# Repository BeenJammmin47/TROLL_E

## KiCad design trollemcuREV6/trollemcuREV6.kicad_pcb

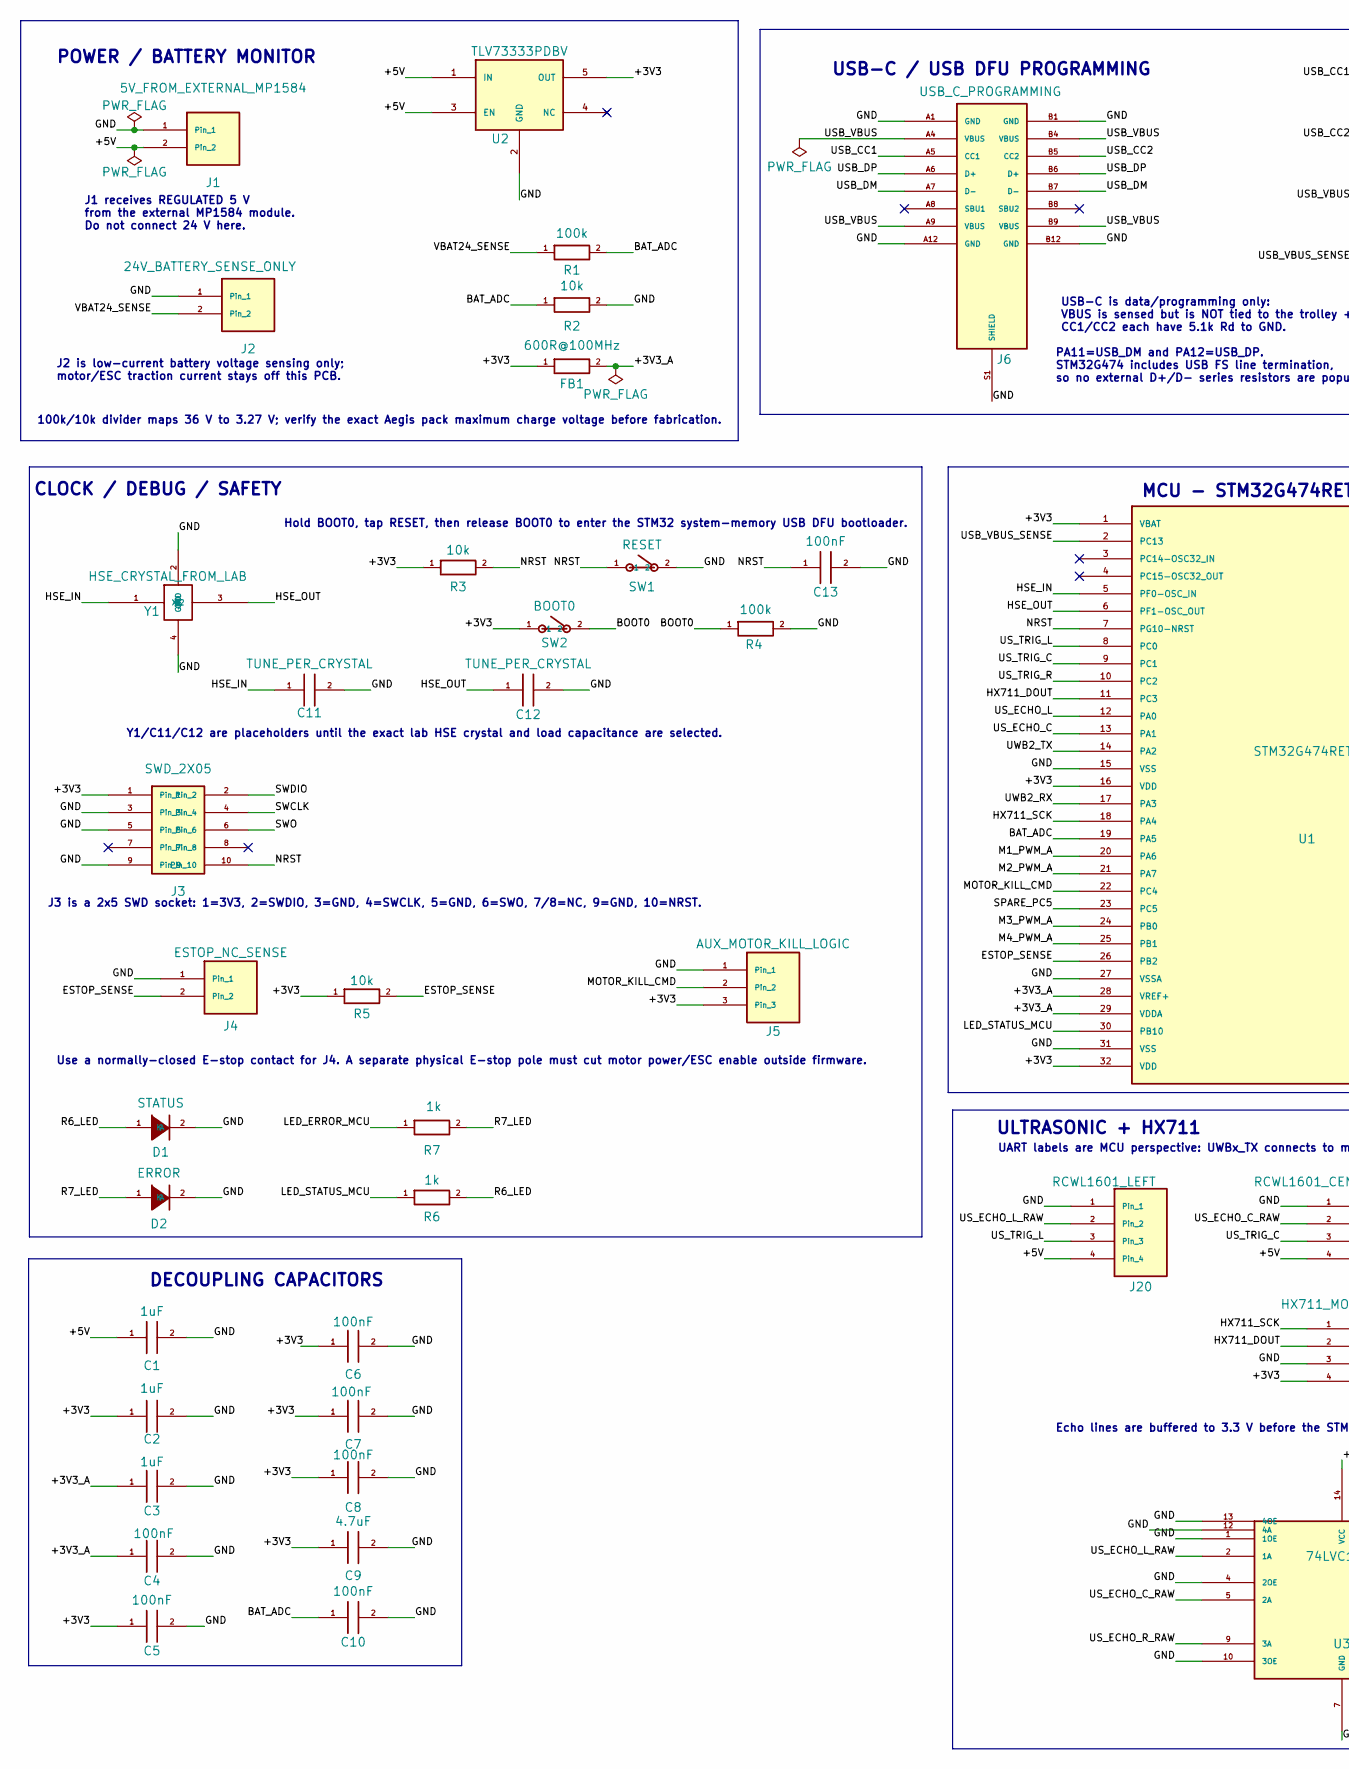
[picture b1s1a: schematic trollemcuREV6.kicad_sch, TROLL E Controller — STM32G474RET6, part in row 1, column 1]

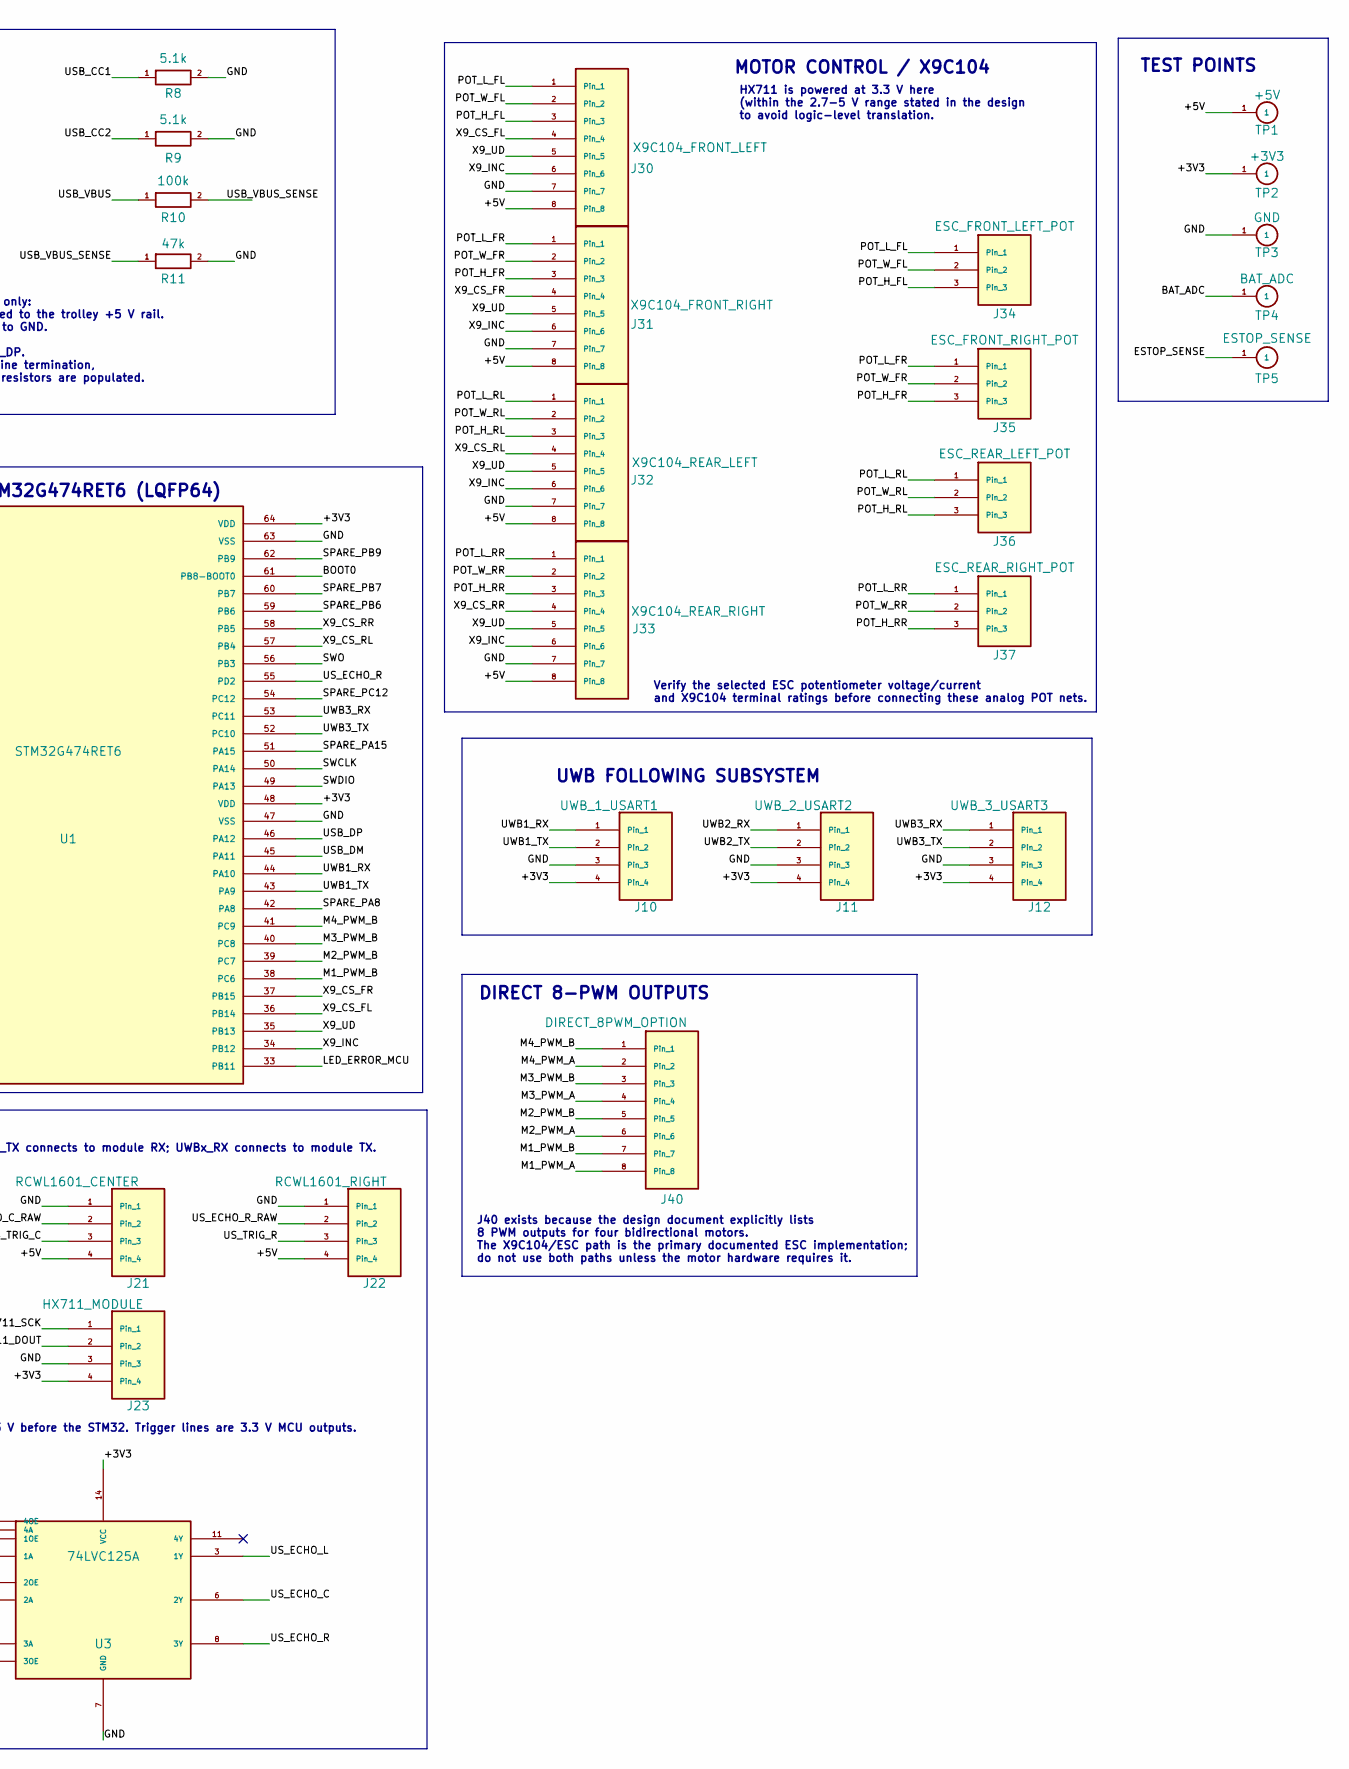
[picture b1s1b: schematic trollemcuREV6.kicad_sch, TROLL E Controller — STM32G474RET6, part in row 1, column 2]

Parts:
C1, C2, C3: 1uF; C_0805_2012Metric
C4, C5, C6, C7, C8, C10, C13: 100nF; C_0805_2012Metric
C9: 4.7uF; C_0805_2012Metric
C11, C12: TUNE_PER_CRYSTAL; C_0805_2012Metric
D1: STATUS; LED_0805_2012Metric
D2: ERROR; LED_0805_2012Metric
FB1: 600R@100MHz; R_0805_2012Metric
J1: 5V_FROM_EXTERNAL_MP1584; PinSocket_1x02_P2.54mm_Vertical
J2: 24V_BATTERY_SENSE_ONLY; PinSocket_1x02_P2.54mm_Vertical
J3: SWD_2X05; PinSocket_2x05_P2.54mm_Vertical
J4: ESTOP_NC_SENSE; PinSocket_1x02_P2.54mm_Vertical
J5: AUX_MOTOR_KILL_LOGIC; PinSocket_1x03_P2.54mm_Vertical
J6: USB_C_PROGRAMMING; USB_C_Receptacle_GCT_USB4085
J10: UWB_1_USART1; PinSocket_1x04_P2.54mm_Vertical
J11: UWB_2_USART2; PinSocket_1x04_P2.54mm_Vertical
J12: UWB_3_USART3; PinSocket_1x04_P2.54mm_Vertical
J20: RCWL1601_LEFT; PinSocket_1x04_P2.54mm_Vertical
J21: RCWL1601_CENTER; PinSocket_1x04_P2.54mm_Vertical
J22: RCWL1601_RIGHT; PinSocket_1x04_P2.54mm_Vertical
J23: HX711_MODULE; PinSocket_1x04_P2.54mm_Vertical
J30: X9C104_FRONT_LEFT; PinHeader_1x08_P2.54mm_Vertical
J31: X9C104_FRONT_RIGHT; PinHeader_1x08_P2.54mm_Vertical
J32: X9C104_REAR_LEFT; PinHeader_1x08_P2.54mm_Vertical
J33: X9C104_REAR_RIGHT; PinHeader_1x08_P2.54mm_Vertical
J34: ESC_FRONT_LEFT_POT; PinSocket_1x03_P2.54mm_Vertical
J35: ESC_FRONT_RIGHT_POT; PinSocket_1x03_P2.54mm_Vertical
J36: ESC_REAR_LEFT_POT; PinSocket_1x03_P2.54mm_Vertical
J37: ESC_REAR_RIGHT_POT; PinSocket_1x03_P2.54mm_Vertical
J40: DIRECT_8PWM_OPTION; PinHeader_1x08_P2.54mm_Vertical
R1, R4, R10: 100k; R_0805_2012Metric
R2, R3, R5: 10k; R_0805_2012Metric
R6, R7: 1k; R_0805_2012Metric
R8, R9: 5.1k; R_0805_2012Metric
R11: 47k; R_0805_2012Metric
SW1: RESET; SW_Push_SPST_NO_Alps_SKRK
SW2: BOOT0; SW_Push_SPST_NO_Alps_SKRK
TP1: +5V; TestPoint_Pad_4.0x4.0mm
TP2: +3V3; TestPoint_Pad_4.0x4.0mm
TP3: GND; TestPoint_Pad_4.0x4.0mm
TP4: BAT_ADC; TestPoint_Pad_4.0x4.0mm
TP5: ESTOP_SENSE; TestPoint_Pad_4.0x4.0mm
U1: STM32G474RET6; LQFP-64_10x10mm_P0.5mm
U2: TLV73333PDBV; SOT-23-5
U3: 74LVC125A; SOIC-14_3.9x8.7mm_P1.27mm
Y1: HSE_CRYSTAL_FROM_LAB; Crystal_SMD_5032-4Pin_5.0x3.2mm

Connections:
/+3V3: C2.1, C5.1, C6.1, C7.1, C8.1, C9.1, FB1.1, J3.1, J5.3, J10.4, J11.4, J12.4, J23.4, R3.1, R5.1, SW2.1, TP2.1 (1_1), U1.1 (VBAT), U1.16 (VDD), U1.32 (VDD), U1.48 (VDD), U1.64 (VDD), U2.5 (OUT), U3.14 (VCC)
/+3V3_A: C3.1, C4.1, FB1.2, U1.28 (VREF+), U1.29 (VDDA)
/+5V: C1.1, J1.2, J20.4, J21.4, J22.4, J30.8, J31.8, J32.8, J33.8, TP1.1 (1_1), U2.1 (IN), U2.3 (EN)
/BAT_ADC: C10.1, R1.2, R2.1, TP4.1 (1_1), U1.19 (PA5)
/BOOT0: R4.1, SW2.2, U1.61 (PB8-BOOT0)
/ESTOP_SENSE: J4.2, R5.2, TP5.1 (1_1), U1.26 (PB2)
/GND: C1.2, C2.2, C3.2, C4.2, C5.2, C6.2, C7.2, C8.2, C9.2, C10.2, C11.2, C12.2, C13.2, D1.2 (K), D2.2 (K), J1.1, J2.1, J3.3, J3.5, J3.9, J4.1, J5.1, J6.A1 (GND_A1), J6.A12 (GND_A12), J6.B1 (GND_B1), J6.B12 (GND_B12), J6.S1 (SHIELD), J6.SH (SHIELD_S1), J10.3, J11.3, J12.3, J20.1, J21.1, J22.1, J23.3, J30.7, J31.7, J32.7, J33.7, R2.2, R4.2, R8.2, R9.2, R11.2, SW1.2, TP3.1 (1_1), U1.15 (VSS), U1.27 (VSSA), U1.31 (VSS), U1.47 (VSS), U1.63 (VSS), U2.2 (GND), U3.1 (1OE), U3.4 (2OE), U3.7 (GND), U3.10 (3OE), U3.12 (4A), U3.13 (4OE), Y1.2 (GND), Y1.4 (GND)
/HSE_IN: C11.1, U1.5 (PF0-OSC_IN), Y1.1 (X1)
/HSE_OUT: C12.1, U1.6 (PF1-OSC_OUT), Y1.3 (X2)
/HX711_DOUT: J23.2, U1.11 (PC3)
/HX711_SCK: J23.1, U1.18 (PA4)
/LED_ERROR_MCU: R7.1, U1.33 (PB11)
/LED_STATUS_MCU: R6.1, U1.30 (PB10)
/M1_PWM_A: J40.8, U1.20 (PA6)
/M1_PWM_B: J40.7, U1.38 (PC6)
/M2_PWM_A: J40.6, U1.21 (PA7)
/M2_PWM_B: J40.5, U1.39 (PC7)
/M3_PWM_A: J40.4, U1.24 (PB0)
/M3_PWM_B: J40.3, U1.40 (PC8)
/M4_PWM_A: J40.2, U1.25 (PB1)
/M4_PWM_B: J40.1, U1.41 (PC9)
/MOTOR_KILL_CMD: J5.2, U1.22 (PC4)
/NRST: C13.1, J3.10, R3.2, SW1.1, U1.7 (PG10-NRST)
/POT_H_FL: J30.3, J34.3
/POT_H_FR: J31.3, J35.3
/POT_H_RL: J32.3, J36.3
/POT_H_RR: J33.3, J37.3
/POT_L_FL: J30.1, J34.1
/POT_L_FR: J31.1, J35.1
/POT_L_RL: J32.1, J36.1
/POT_L_RR: J33.1, J37.1
/POT_W_FL: J30.2, J34.2
/POT_W_FR: J31.2, J35.2
/POT_W_RL: J32.2, J36.2
/POT_W_RR: J33.2, J37.2
/R6_LED: D1.1 (A), R6.2
/R7_LED: D2.1 (A), R7.2
/SPARE_PA8: U1.42 (PA8)
/SPARE_PA15: U1.51 (PA15)
/SPARE_PB6: U1.59 (PB6)
/SPARE_PB7: U1.60 (PB7)
/SPARE_PB9: U1.62 (PB9)
/SPARE_PC5: U1.23 (PC5)
/SPARE_PC12: U1.54 (PC12)
/SWCLK: J3.4, U1.50 (PA14)
/SWDIO: J3.2, U1.49 (PA13)
/SWO: J3.6, U1.56 (PB3)
/USB_CC1: J6.A5 (CC1_A5), R8.1
/USB_CC2: J6.B5 (CC2_B5), R9.1
/USB_DM: J6.A7 (D-_A7), J6.B7 (D-_B7), U1.45 (PA11)
/USB_DP: J6.A6 (D+_A6), J6.B6 (D+_B6), U1.46 (PA12)
/USB_VBUS: J6.A4 (VBUS_A4), J6.A9 (VBUS_A9), J6.B4 (VBUS_B4), J6.B9 (VBUS_B9), R10.1
/USB_VBUS_SENSE: R10.2, R11.1, U1.2 (PC13)
/US_ECHO_C: U1.13 (PA1), U3.6 (2Y)
/US_ECHO_C_RAW: J21.2, U3.5 (2A)
/US_ECHO_L: U1.12 (PA0), U3.3 (1Y)
/US_ECHO_L_RAW: J20.2, U3.2 (1A)
/US_ECHO_R: U1.55 (PD2), U3.8 (3Y)
/US_ECHO_R_RAW: J22.2, U3.9 (3A)
/US_TRIG_C: J21.3, U1.9 (PC1)
/US_TRIG_L: J20.3, U1.8 (PC0)
/US_TRIG_R: J22.3, U1.10 (PC2)
/UWB1_RX: J10.1, U1.44 (PA10)
/UWB1_TX: J10.2, U1.43 (PA9)
/UWB2_RX: J11.1, U1.17 (PA3)
/UWB2_TX: J11.2, U1.14 (PA2)
/UWB3_RX: J12.1, U1.53 (PC11)
/UWB3_TX: J12.2, U1.52 (PC10)
/VBAT24_SENSE: J2.2, R1.1
/X9_CS_FL: J30.4, U1.36 (PB14)
/X9_CS_FR: J31.4, U1.37 (PB15)
/X9_CS_RL: J32.4, U1.57 (PB4)
/X9_CS_RR: J33.4, U1.58 (PB5)
/X9_INC: J30.6, J31.6, J32.6, J33.6, U1.34 (PB12)
/X9_UD: J30.5, J31.5, J32.5, J33.5, U1.35 (PB13)

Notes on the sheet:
TEST POINTS
Verify the selected ESC potentiometer voltage/current and X9C104 terminal ratings before connecting these analog POT nets.
UWB FOLLOWING SUBSYSTEM
USB-C is data/programming only: VBUS is sensed but is NOT tied to the trolley +5 V rail. CC1/CC2 each have 5.1k Rd to GND.
CLOCK / DEBUG / SAFETY
Hold BOOT0, tap RESET, then release BOOT0 to enter the STM32 system-memory USB DFU bootloader.
J2 is low-current battery voltage sensing only; motor/ESC traction current stays off this PCB.
Use a normally-closed E-stop contact for J4. A separate physical E-stop pole must cut motor power/ESC enable outside firmware.
J3 is a 2x5 SWD socket: 1=3V3, 2=SWDIO, 3=GND, 4=SWCLK, 5=GND, 6=SWO, 7/8=NC, 9=GND, 10=NRST.
UART labels are MCU perspective: UWBx_TX connects to module RX; UWBx_RX connects to module TX.
ULTRASONIC + HX711
DIRECT 8-PWM OUTPUTS
DECOUPLING CAPACITORS
J40 exists because the design document explicitly lists 8 PWM outputs for four bidirectional motors. The X9C104/ESC path is the primary documented ESC implementation; do not use both paths unless the motor hardware requires it.
Y1/C11/C12 are placeholders until the exact lab HSE crystal and load capacitance are selected.
MCU - STM32G474RET6 (LQFP64)
USB-C / USB DFU PROGRAMMING
100k/10k divider maps 36 V to 3.27 V; verify the exact Aegis pack maximum charge voltage before fabrication.
J1 receives REGULATED 5 V from the external MP1584 module. Do not connect 24 V here.
PA11=USB_DM and PA12=USB_DP. STM32G474 includes USB FS line termination, so no external D+/D- series resistors are populated.
Echo lines are buffered to 3.3 V before the STM32. Trigger lines are 3.3 V MCU outputs.
POWER / BATTERY MONITOR
MOTOR CONTROL / X9C104
HX711 is powered at 3.3 V here (within the 2.7-5 V range stated in the design to avoid logic-level translation.

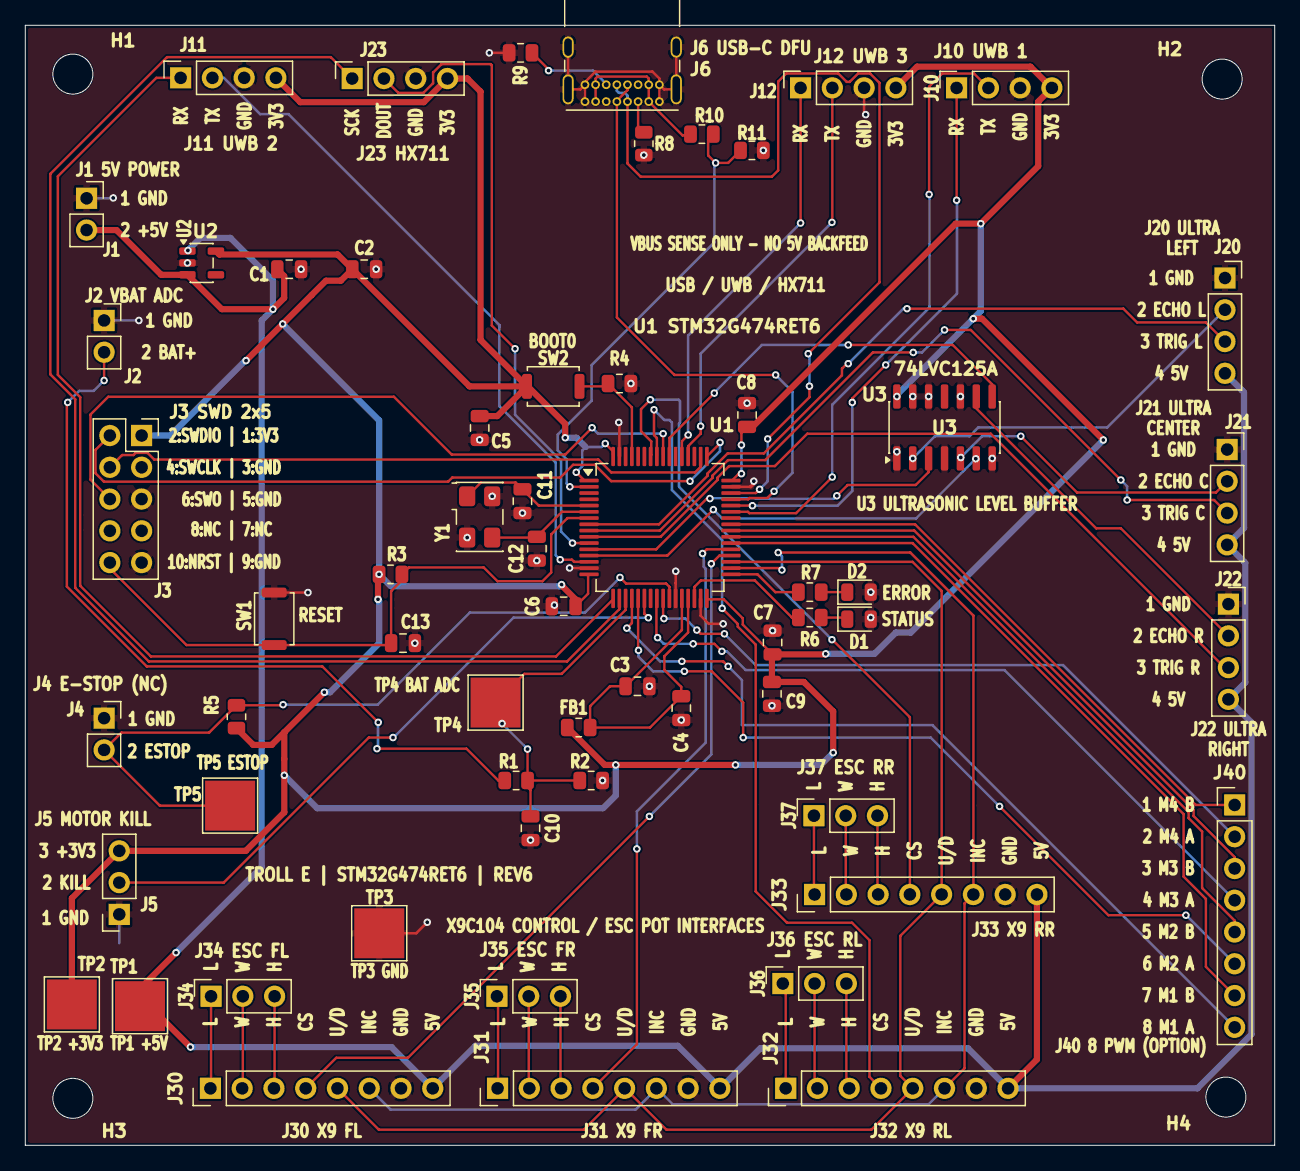
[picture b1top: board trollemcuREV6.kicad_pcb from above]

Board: 2 copper layers, 99.9 x 89.6 mm, 64 parts (0 on the bottom side), 68 nets.

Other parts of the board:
H1, H2, H3, H4: MountingHole_3.2mm_M3

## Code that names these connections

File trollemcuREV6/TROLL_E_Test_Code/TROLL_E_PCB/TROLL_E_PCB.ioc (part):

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Mcu.Name=STM32G474R(B-C-E)Tx
Mcu.Package=LQFP64
Mcu.UserName=STM32G474RETx
PA0.GPIOParameters=GPIO_Label
PA0.GPIO_Label=US_ECHO_L
PA0.Signal=GPIO_Input
PA1.GPIOParameters=GPIO_Label
PA1.GPIO_Label=US_ECHO_C
PA1.Signal=GPIO_Input
PA10.GPIOParameters=GPIO_Label
PA10.GPIO_Label=UWB1_RX
PA10.Mode=Asynchronous
PA10.Signal=USART1_RX
PA11.Mode=Device
PA11.Signal=USB_DM
PA12.Mode=Device
PA12.Signal=USB_DP
PA13.Mode=Serial_Wire
PA13.Signal=SYS_JTMS-SWDIO
PA14.Mode=Serial_Wire
PA14.Signal=SYS_JTCK-SWCLK
PA2.GPIOParameters=GPIO_Label
PA2.GPIO_Label=UWB2_TX
PA2.Mode=Asynchronous
PA2.Signal=USART2_TX
PA3.GPIOParameters=GPIO_Label
PA3.GPIO_Label=UWB2_RX
PA3.Mode=Asynchronous
PA3.Signal=USART2_RX
PA4.GPIOParameters=GPIO_PuPd,GPIO_Label
PA4.GPIO_Label=HX711_SCK
PA4.GPIO_PuPd=GPIO_NOPULL
PA4.Signal=GPIO_Output
PA6.GPIOParameters=GPIO_Label
PA6.GPIO_Label=M1_SPD_B
PA6.Signal=S_TIM3_CH1
PA7.GPIOParameters=GPIO_Label
PA7.GPIO_Label=M2_SPD_B
PA7.Signal=S_TIM3_CH2
PA9.GPIOParameters=GPIO_Label
PA9.GPIO_Label=UWB1_TX
PA9.Mode=Asynchronous
PA9.Signal=USART1_TX
PB0.GPIOParameters=GPIO_Label
PB0.GPIO_Label=M3_SPD_B
PB0.Signal=S_TIM3_CH3
PB1.GPIOParameters=GPIO_Label
PB1.GPIO_Label=M4_SPD_B
PB1.Signal=S_TIM3_CH4
PB10.GPIOParameters=GPIO_Label
PB10.GPIO_Label=LED_STATUS_MCU
PB10.Signal=GPIO_Output
PB11.GPIOParameters=GPIO_Label
PB11.GPIO_Label=LED_ERROR_MCU
PB11.Signal=GPIO_Output
PB2.GPIOParameters=GPIO_Label
PB2.GPIO_Label=ESTOP_SENSE
PB2.Signal=GPIO_Input
PC0.GPIOParameters=GPIO_Label
PC0.GPIO_Label=US_TRIG_L
PC0.Signal=GPIO_Output
PC1.GPIOParameters=GPIO_Label
PC1.GPIO_Label=US_TRIG_C
PC1.Signal=GPIO_Output
PC10.GPIOParameters=GPIO_Label
PC10.GPIO_Label=LiDAR_TX
PC10.Mode=Asynchronous
PC10.Signal=USART3_TX
PC11.GPIOParameters=GPIO_Label
PC11.GPIO_Label=LiDAR_RX
PC11.Mode=Asynchronous
PC11.Signal=USART3_RX
PC2.GPIOParameters=GPIO_Label
PC2.GPIO_Label=US_TRIG_R
PC2.Signal=GPIO_Output
PC3.GPIOParameters=GPIO_PuPd,GPIO_Label
PC3.GPIO_Label=HX711_DOUT
PC3.GPIO_PuPd=GPIO_PULLUP
PC3.Signal=GPIO_Input
PC4.GPIOParameters=PinState,GPIO_Label
PC4.GPIO_Label=MOTOR_KILL_CMD
PC4.PinState=GPIO_PIN_SET
PC4.Signal=GPIO_Output
PC6.GPIOParameters=GPIO_Label
PC6.GPIO_Label=M1_DIR_W
PC6.Signal=GPIO_Output
PC7.GPIOParameters=GPIO_Label
PC7.GPIO_Label=M2_DIR_W
PC7.Signal=GPIO_Output
PC8.GPIOParameters=GPIO_Label
PC8.GPIO_Label=M3_DIR_W
PC8.Signal=GPIO_Output
PC9.GPIOParameters=GPIO_Label
PC9.GPIO_Label=M4_DIR_W
PC9.Signal=GPIO_Output
PD2.GPIOParameters=GPIO_Label
PD2.GPIO_Label=US_ECHO_R
PD2.Signal=GPIO_Input
PF0-OSC_IN.Mode=HSE-External-Oscillator
PF0-OSC_IN.Signal=RCC_OSC_IN
PF1-OSC_OUT.Mode=HSE-External-Oscillator
PF1-OSC_OUT.Signal=RCC_OSC_OUT
RCC.HSE_VALUE=8000000
RCC.SYSCLKFreq_VALUE=170000000
RCC.SYSCLKSource=RCC_SYSCLKSOURCE_PLLCLK
board=custom

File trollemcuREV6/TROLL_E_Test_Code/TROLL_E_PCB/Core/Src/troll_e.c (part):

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 * NOW (progress demo -- one of each sensor):
 *   TIM2      internal clock, Prescaler 169, Period 4294967295 -> 1 MHz microsecond counter
 *   Motor speed, one of two ways (picked automatically: DAC enabled in CubeMX -> DAC mode):
 *   DAC mode: DAC2 OUT1 on PA6, external pin, buffer ON -> one voltage for all four blue wires
 *   PWM mode: TIM3 CH1..CH4 on PA6 / PA7 / PB0 / PB1, PWM Generation, Prescaler 0, Period 8499
 *             -> each motor's blue wire gets its own pin (J40 pins 8 / 6 / 4 / 2)
 *                                                              -> motor speed voltage (all blue wires)
 *   TIM3      PWM mode only
 *   GPIO outputs M1_DIR_W..M4_DIR_W (or M1_DIR / M1_PWM_B)     -> motor direction (white wires)
 *             PCB: PC6..PC9.  Nucleo demo: M1_PWM_B moved to PB5 (D4), M2_PWM_B on PC7 (D9).
 *   USART3    PC10 TX / PC11 RX, 460800 8N1, RX DMA Circular,
 *             USART3 global interrupt ON                       -> lidar (PCB header J12)
 *   LPUART1   PA2 / PA3, 115200 8N1                            -> debug terminal (ST-LINK USB)
 *   GPIO labels (= PCB net names):
 *     US_TRIG_C  PC1 output        US_ECHO_C  PA1 input        (center ultrasonic, J21)
 *     HX711_SCK  PA4 output        HX711_DOUT PC3 input, pull-up (J23)
 *
 * AFTER THE DEMO:
 *     US_TRIG_L  PC0 output        US_ECHO_L  PA0 input        (left ultrasonic, J20)
 *     US_TRIG_R  PC2 output        US_ECHO_R  PD2 input        (right ultrasonic, J22)
 *   USART1    PA9 TX / PA10 RX, 115200 8N1, RX DMA Circular,
 *             USART1 global interrupt ON                       -> UWB 1 (J10): cart UWB board (tag) sends "D,<cm>"
 *   USART2    PCB: PA2 TX / PA3 RX (J11), same settings as USART1  -> UWB 2 (J11): second cart tag
 *             Nucleo: PB3 / PB4 instead, because PA2/PA3 are the ST-LINK terminal there
 *   On the PCB, LPUART1 is not available (PA2/PA3 are UWB 2): the terminal runs over USB-C
 *   instead (USB Device, CDC class). The code switches automatically -- see DEBUG_OVER_USB.
 *
 * PCB (trollemcuREV6) extras, used automatically when the labels exist in CubeMX:
 *   ESTOP_SENSE PB2 (input), MOTOR_KILL_CMD PC4 (output), LED_STATUS_MCU PB10, LED_ERROR_MCU PB11.
 *   Motor direction on the PCB: M1..M4_PWM_B = PC6..PC9 (J40 pins 7,5,3,1); speed = PA6 (J40 pin 8).
 *
 *   Project setting: enable "Use float with printf from newlib-nano (-u _printf_float)"
 *   or every %f below prints blank.
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 *   red = 24 V, black = GND, blue = speed, white = CW/CCW, yellow = FG (open collector, 6 pulses/rev)
 *   MEASURED on our motors (the datasheet table is wrong for them): blue is an ANALOG speed input.
 *     0 V = stop, ~1.1 V = very slow, ~2.2 V = slower, 3.3 V / unconnected = fast.
 *   So D12 (PA6) drives the blue wires with a real voltage from DAC2, not PWM.
 *   Speed % maps linearly from MOTOR_V_MIN (just turning) to MOTOR_V_MAX; 0 % = 0 V. */
#define MOTOR_V_MIN           1.26f  /* volts where a stopped motor starts turning (measured on the PCB:
                                        old m 15; once turning it keeps going down to ~1.19 V) */
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 * Which side is which depends on mounting -- fix these after the wheel test. */
static const GPIO_PinState MOTOR_FWD_LEVEL[4] = { GPIO_PIN_SET, GPIO_PIN_RESET, GPIO_PIN_SET, GPIO_PIN_RESET };

/* Direction pin labels (white wire): M1_DIR_W..M4_DIR_W, M1_DIR..M4_DIR, or the PCB net names M1_PWM_B..M4_PWM_B */
#if defined(M1_DIR_W_Pin)
#  define MDIR_PORT(n) M##n##_DIR_W_GPIO_Port
#  define MDIR_PIN(n)  M##n##_DIR_W_Pin
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} UsSensor;

static const UsSensor usSensors[] = {
  { US_TRIG_C_GPIO_Port, US_TRIG_C_Pin, US_ECHO_C_GPIO_Port, US_ECHO_C_Pin, "US_C" },
  /* Left / right are included automatically once their labels exist in CubeMX */
#if defined(US_TRIG_L_Pin) && defined(US_ECHO_L_Pin)
  { US_TRIG_L_GPIO_Port, US_TRIG_L_Pin, US_ECHO_L_GPIO_Port, US_ECHO_L_Pin, "US_L" },
#endif
#if defined(US_TRIG_R_Pin) && defined(US_ECHO_R_Pin)
  { US_TRIG_R_GPIO_Port, US_TRIG_R_Pin, US_ECHO_R_GPIO_Port, US_ECHO_R_Pin, "US_R" },
#endif
};
#define US_COUNT ((int)(sizeof(usSensors) / sizeof(usSensors[0])))
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
static int hxReady(void)
{
  return HAL_GPIO_ReadPin(HX711_DOUT_GPIO_Port, HX711_DOUT_Pin) == GPIO_PIN_RESET;
}

/* Clock out one 24-bit reading. Interrupts are held off for ~110 us because a
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  __disable_irq();

  for (int i = 0; i < 24; i++) {
    HAL_GPIO_WritePin(HX711_SCK_GPIO_Port, HX711_SCK_Pin, GPIO_PIN_SET);
    delay_us(2);
    value = (value << 1) | (HAL_GPIO_ReadPin(HX711_DOUT_GPIO_Port, HX711_DOUT_Pin) == GPIO_PIN_SET);
    HAL_GPIO_WritePin(HX711_SCK_GPIO_Port, HX711_SCK_Pin, GPIO_PIN_RESET);
    delay_us(2);
  }
  /* 25th pulse: channel A, gain 128 for the next conversion */
  HAL_GPIO_WritePin(HX711_SCK_GPIO_Port, HX711_SCK_Pin, GPIO_PIN_SET);
  delay_us(2);
  HAL_GPIO_WritePin(HX711_SCK_GPIO_Port, HX711_SCK_Pin, GPIO_PIN_RESET);

  if (!primask) __enable_irq();

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
/* ======================================================================
 * PCB-only signals (each compiled in only if its CubeMX label exists)
 *   ESTOP_SENSE    PB2  input, R5 pull-up. J4 = normally-closed e-stop to GND:
 *                       LOW = OK, HIGH = pressed OR J4 unplugged -> STOP
 *   MOTOR_KILL_CMD PC4  output to J5, HIGH = kill (motors stopped), LOW = motors may run
 *   LED_STATUS_MCU PB10 green-ish "alive" LED, blinks once a second
 *   LED_ERROR_MCU  PB11 on when: e-stop, HX711 not answering, or overload
 * ====================================================================== */
static int estopActive(void)
{
#ifdef ESTOP_SENSE_Pin
  return HAL_GPIO_ReadPin(ESTOP_SENSE_GPIO_Port, ESTOP_SENSE_Pin) == GPIO_PIN_SET;
#else
  return 0;
#endif
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
static void killOutput(int kill)
{
#ifdef MOTOR_KILL_CMD_Pin
  HAL_GPIO_WritePin(MOTOR_KILL_CMD_GPIO_Port, MOTOR_KILL_CMD_Pin, kill ? GPIO_PIN_SET : GPIO_PIN_RESET);
#else
  (void)kill;
#endif
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
static void ledService(uint32_t now, int error)
{
#ifdef LED_STATUS_MCU_Pin
  HAL_GPIO_WritePin(LED_STATUS_MCU_GPIO_Port, LED_STATUS_MCU_Pin,
                    ((now / 500U) & 1U) ? GPIO_PIN_SET : GPIO_PIN_RESET);
#endif
#ifdef LED_ERROR_MCU_Pin
  HAL_GPIO_WritePin(LED_ERROR_MCU_GPIO_Port, LED_ERROR_MCU_Pin, error ? GPIO_PIN_SET : GPIO_PIN_RESET);
#else
  (void)error;
#endif
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    if (strcmp(usSensors[i].name, "US_C") == 0) usIdxC = i;
    if (strcmp(usSensors[i].name, "US_R") == 0) usIdxR = i;
  }
  HAL_GPIO_WritePin(HX711_SCK_GPIO_Port, HX711_SCK_Pin, GPIO_PIN_RESET);   /* CLK low keeps HX711 awake */

  uprintf("\r\n=== TROLL-E ===  motor %s (%s speed), lidar %s, uwb %s, steering %s, terminal over %s\r\n",
          MOTOR_ENABLED ? "ENABLED" : "disabled", MOTOR_SPEED_PWM ? "PWM" : "DAC",
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
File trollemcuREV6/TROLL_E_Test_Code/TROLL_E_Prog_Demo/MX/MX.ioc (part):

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Mcu.Name=STM32G474R(B-C-E)Tx
Mcu.Package=LQFP64
Mcu.UserName=STM32G474RETx
PA1.GPIOParameters=GPIO_PuPd,GPIO_Label
PA1.GPIO_Label=US_ECHO_C
PA1.GPIO_PuPd=GPIO_PULLDOWN
PA1.Signal=GPIO_Input
PA13.GPIOParameters=GPIO_Label
PA13.GPIO_Label=T_SWDIO
PA13.Mode=Serial_Wire
PA13.Signal=SYS_JTMS-SWDIO
PA14.GPIOParameters=GPIO_Label
PA14.GPIO_Label=T_SWCLK
PA14.Mode=Serial_Wire
PA14.Signal=SYS_JTCK-SWCLK
PA2.GPIOParameters=GPIO_Label
PA2.GPIO_Label=LPUART1_TX [STLINKV3E_VCP_RX]
PA2.Mode=Asynchronous
PA2.Signal=LPUART1_TX
PA3.GPIOParameters=GPIO_Label
PA3.GPIO_Label=LPUART1_RX [STLINKV3E_VCP_TX]
PA3.Mode=Asynchronous
PA3.Signal=LPUART1_RX
PA4.GPIOParameters=GPIO_Label
PA4.GPIO_Label=HX711_SCK
PA4.Signal=GPIO_Output
PA6.Signal=COMP_DAC21_group
PA7.Signal=S_TIM3_CH2
PB0.Signal=S_TIM3_CH3
PB1.Signal=S_TIM3_CH4
PB3.GPIOParameters=GPIO_Label
PB3.GPIO_Label=T_SWO
PB3.Signal=SYS_JTDO-SWO
PB5.GPIOParameters=GPIO_Label
PB5.GPIO_Label=M1_PWM_B
PB5.Signal=GPIO_Output
PC1.GPIOParameters=GPIO_Label
PC1.GPIO_Label=US_TRIG_C
PC1.Signal=GPIO_Output
PC10.Mode=Asynchronous
PC10.Signal=USART3_TX
PC11.Mode=Asynchronous
PC11.Signal=USART3_RX
PC14-OSC32_IN.GPIOParameters=GPIO_Label
PC14-OSC32_IN.GPIO_Label=RCC_OSC32_IN
PC14-OSC32_IN.Signal=RCC_OSC32_IN
PC15-OSC32_OUT.GPIOParameters=GPIO_Label
PC15-OSC32_OUT.GPIO_Label=RCC_OSC32_OUT
PC15-OSC32_OUT.Signal=RCC_OSC32_OUT
PC3.GPIOParameters=GPIO_PuPd,GPIO_Label
PC3.GPIO_Label=HX711_DOUT
PC3.GPIO_PuPd=GPIO_PULLUP
PC3.Signal=GPIO_Input
PC7.GPIOParameters=GPIO_Label
PC7.GPIO_Label=M2_PWM_B
PC7.Signal=GPIO_Output
PC8.GPIOParameters=GPIO_Label
PC8.GPIO_Label=M3_PWM_B
PC8.Signal=GPIO_Output
PC9.GPIOParameters=GPIO_Label
PC9.GPIO_Label=M4_PWM_B
PC9.Signal=GPIO_Output
PF0-OSC_IN.GPIOParameters=GPIO_Label
PF0-OSC_IN.GPIO_Label=RCC_OSC_IN
PF0-OSC_IN.Signal=RCC_OSC_IN
PF1-OSC_OUT.GPIOParameters=GPIO_Label
PF1-OSC_OUT.GPIO_Label=RCC_OSC_OUT
PF1-OSC_OUT.Signal=RCC_OSC_OUT
RCC.HSE_VALUE=24000000
RCC.SYSCLKFreq_VALUE=170000000
RCC.SYSCLKSource=RCC_SYSCLKSOURCE_PLLCLK
board=NUCLEO-G474RE
boardIOC=true
